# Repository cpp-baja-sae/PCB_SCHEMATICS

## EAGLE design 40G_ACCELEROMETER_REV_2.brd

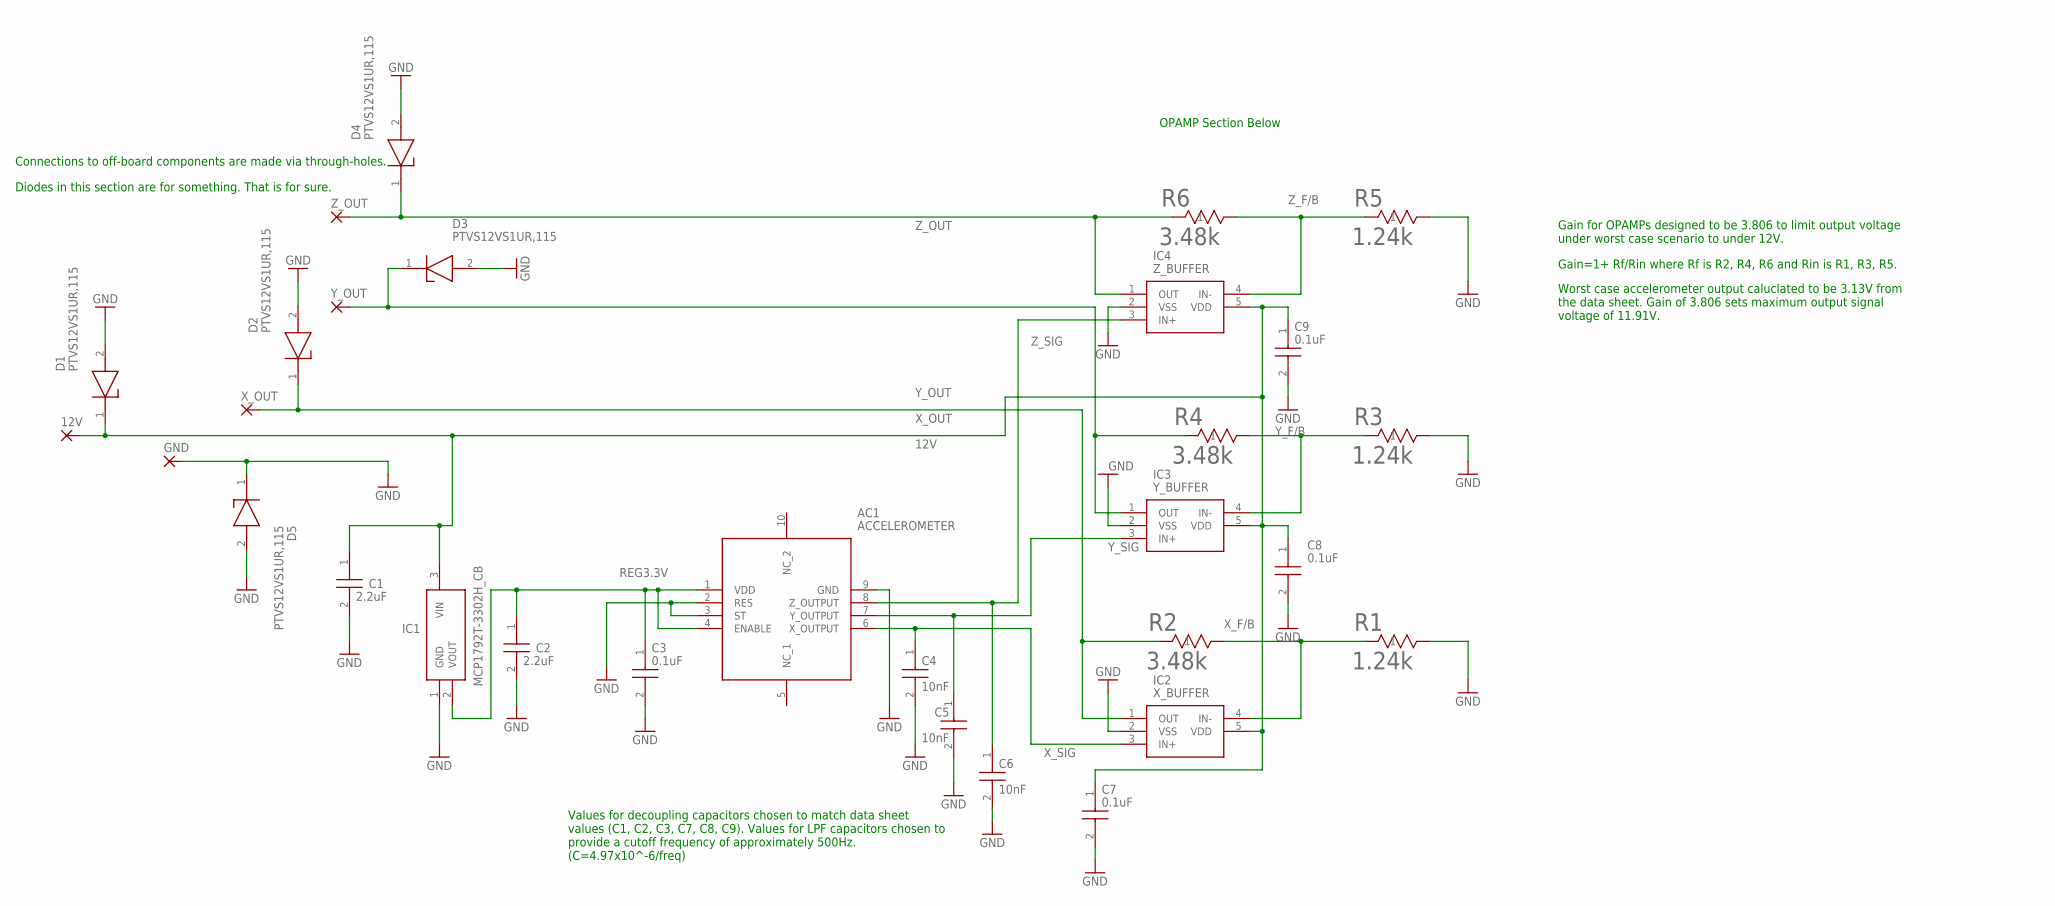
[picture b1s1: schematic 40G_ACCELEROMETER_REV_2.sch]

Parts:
12V: 2,54/1,1
AC1: ACCELEROMETER; KX2201072
C1, C2: 2.2uF; CAPC1608X90N
C3, C7, C8, C9: 0.1uF; CAPC1608X90N
C4, C5, C6: 10nF; CAPC1608X90N
D1, D2, D3, D4, D5: PTVS12VS1UR,115; SOD123W
GND: 2,54/1,1
IC1: MCP1792T-3302H_CB; SOT95P255X145-3N
IC2: X_BUFFER; SOT95P275X110-5N
IC3: Y_BUFFER; SOT95P275X110-5N
IC4: Z_BUFFER; SOT95P275X110-5N
R1, R3, R5: 1.24k; RES_TNPW0402_VIS
R2, R4, R6: 3.48k; RES_TNPW0402_VIS
X_OUT: 2,54/1,1
Y_OUT: 2,54/1,1
Z_OUT: 2,54/1,1

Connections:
12V: 12V.1, C1.1, C7.1, C8.1, C9.1, D1.1 (K), IC1.3 (VIN), IC2.5 (VDD), IC3.5 (VDD), IC4.5 (VDD)
GND: AC1.2 (RES), AC1.3 (ST), AC1.9 (GND), C1.2, C2.2, C3.2, C4.2, C5.2, C6.2, C7.2, C8.2, C9.2, D1.2 (A), D2.2 (A), D3.2 (A), D4.2 (A), D5.1 (K), D5.2 (A), GND.1, IC1.1 (GND), IC2.2 (VSS), IC3.2 (VSS), IC4.2 (VSS), R1.2, R3.2, R5.2
REG3.3V: AC1.1 (VDD), AC1.4 (ENABLE), C2.1, C3.1, IC1.2 (VOUT)
X_F/B: IC2.4 (IN-), R1.1, R2.2
X_OUT: D2.1 (K), IC2.1 (OUT), R2.1, X_OUT.1
X_SIG: AC1.6 (X_OUTPUT), C4.1, IC2.3 (IN+)
Y_F/B: IC3.4 (IN-), R3.1, R4.2
Y_OUT: D3.1 (K), IC3.1 (OUT), R4.1, Y_OUT.1
Y_SIG: AC1.7 (Y_OUTPUT), C5.1, IC3.3 (IN+)
Z_F/B: IC4.4 (IN-), R5.1, R6.2
Z_OUT: D4.1 (K), IC4.1 (OUT), R6.1, Z_OUT.1
Z_SIG: AC1.8 (Z_OUTPUT), C6.1, IC4.3 (IN+)

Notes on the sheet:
Gain for OPAMPs designed to be 3.806 to limit output voltage under worst case scenario to under 12V.
Values for decoupling capacitors chosen to match data sheet values (C1, C2, C3, C7, C8, C9). Values for LPF capacitors chosen to provide a cutoff frequency of approximately 500Hz. (C=4.97x10^-6/freq)
OPAMP Section Below
Gain=1+ Rf/Rin where Rf is R2, R4, R6 and Rin is R1, R3, R5.
Worst case accelerometer output caluclated to be 3.13V from the data sheet. Gain of 3.806 sets maximum output signal voltage of 11.91V.
Diodes in this section are for something. That is for sure.
Connections to off-board components are made via through-holes.

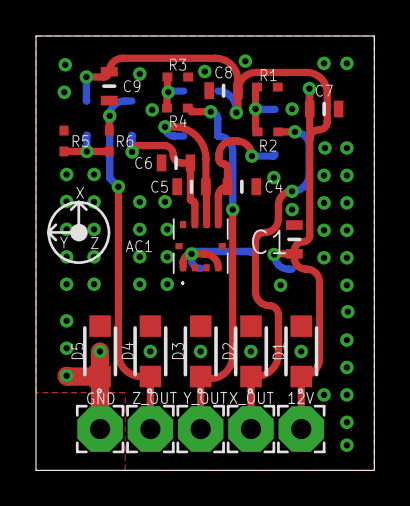
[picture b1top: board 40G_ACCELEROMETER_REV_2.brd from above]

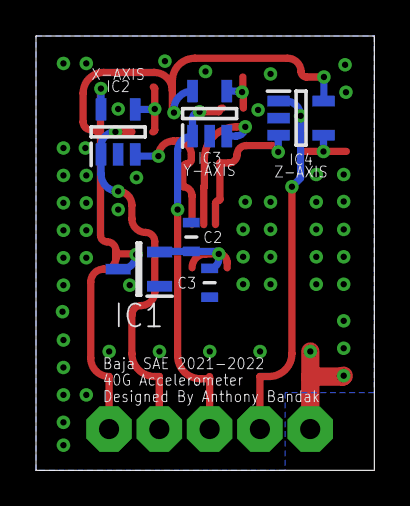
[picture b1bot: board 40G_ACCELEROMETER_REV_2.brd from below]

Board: 2 copper layers, 18.8 x 24.1 mm, 30 parts (6 on the bottom side), 12 nets.

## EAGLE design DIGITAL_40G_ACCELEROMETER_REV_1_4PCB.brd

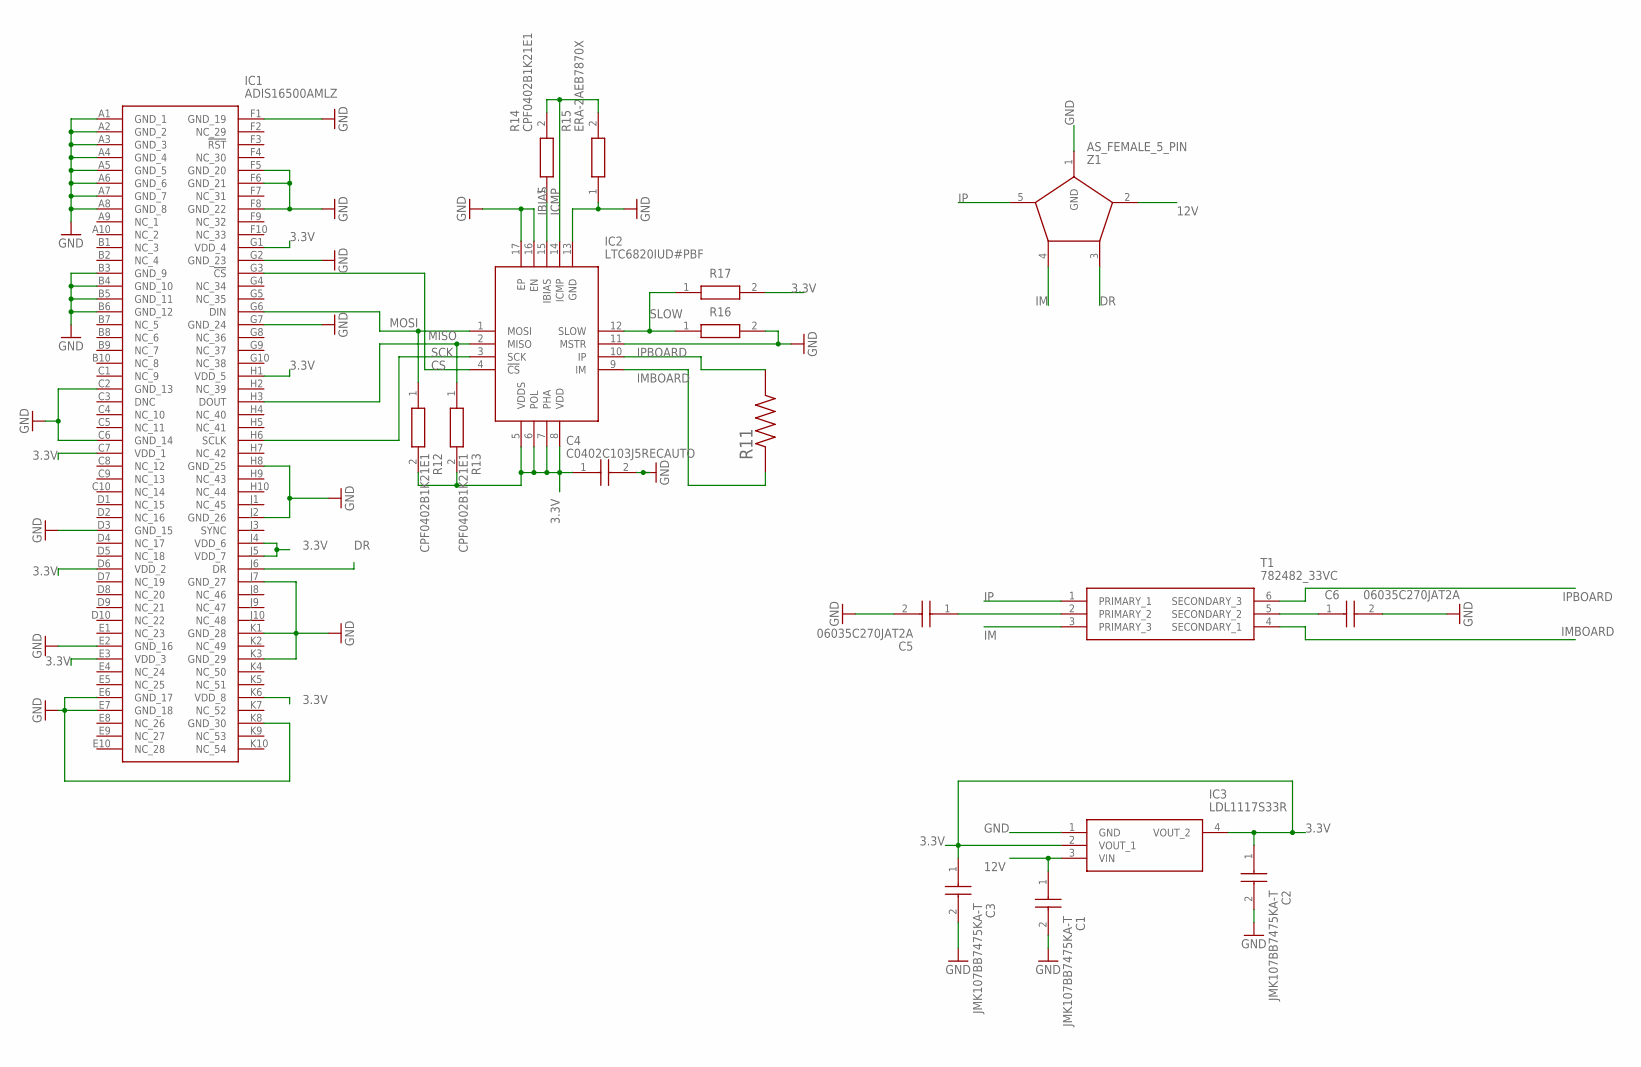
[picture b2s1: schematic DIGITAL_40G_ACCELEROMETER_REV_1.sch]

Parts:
C1, C2, C3: JMK107BB7475KA-T; CAPC1608X90N
C4: C0402C103J5RECAUTO; CAPC1005X55N
C5, C6: 06035C270JAT2A; CAPC1608X90N
IC1: ADIS16500AMLZ; BGA100C127P10X10_1500X1500X608
IC2: LTC6820IUD#PBF; QFN50P300X300X80-17N
IC3: LDL1117S33R; SOT230P700X180-4N
R11: 100; RESC1005X40N
R12, R13, R14: CPF0402B1K21E1; RESC1005X35N
R15: ERA-2AEB7870X; ERA2AED122X
R16, R17: CRG0402ZR; RESC1005X40N
T1: 782482_33VC; DIP1016W60P254L914H635Q6N
Z1: AS_FEMALE_5_PIN

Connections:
3.3V: C2.1, C3.1, C4.1, IC1.C7 (VDD_1), IC1.D6 (VDD_2), IC1.E3 (VDD_3), IC1.G1 (VDD_4), IC1.H1 (VDD_5), IC1.J4 (VDD_6), IC1.J5 (VDD_7), IC1.K6 (VDD_8), IC2.5 (VDDS), IC2.6 (POL), IC2.7 (PHA), IC2.8 (VDD), IC3.2 (VOUT_1), IC3.4 (VOUT_2), R12.2, R13.2, R17.2
12V: C1.1, IC3.3 (VIN), Z1.2 (1)
CS: IC1.G3 (!CS), IC2.4 (!CS)
DR: IC1.J6 (DR), Z1.3 (2)
GND: C1.2, C2.2, C3.2, C4.2, C5.2, C6.2, IC1.A1 (GND_1), IC1.A2 (GND_2), IC1.A3 (GND_3), IC1.A4 (GND_4), IC1.A5 (GND_5), IC1.A6 (GND_6), IC1.A7 (GND_7), IC1.A8 (GND_8), IC1.B3 (GND_9), IC1.B4 (GND_10), IC1.B5 (GND_11), IC1.B6 (GND_12), IC1.C2 (GND_13), IC1.C6 (GND_14), IC1.D3 (GND_15), IC1.E2 (GND_16), IC1.E6 (GND_17), IC1.E7 (GND_18), IC1.F1 (GND_19), IC1.F5 (GND_20), IC1.F6 (GND_21), IC1.F8 (GND_22), IC1.G2 (GND_23), IC1.G7 (GND_24), IC1.H8 (GND_25), IC1.J2 (GND_26), IC1.J7 (GND_27), IC1.K1 (GND_28), IC1.K3 (GND_29), IC1.K8 (GND_30), IC2.11 (MSTR), IC2.13 (GND), IC2.16 (EN), IC2.17 (EP), IC3.1 (GND), R15.1, R16.2, Z1.1 (GND)
IBIAS: IC2.15 (IBIAS), R14.1
ICMP: IC2.14 (ICMP), R14.2, R15.2
IM: T1.3 (PRIMARY_3), Z1.4 (3)
IMBOARD: IC2.9 (IM), R11.1, T1.4 (SECONDARY_1)
IP: T1.1 (PRIMARY_1), Z1.5 (4)
IPBOARD: IC2.10 (IP), R11.2, T1.6 (SECONDARY_3)
MISO: IC1.H3 (DOUT), IC2.2 (MISO), R13.1
MOSI: IC1.G6 (DIN), IC2.1 (MOSI), R12.1
unnamed: C6.1, T1.5 (SECONDARY_2)
unnamed: C5.1, T1.2 (PRIMARY_2)
SCK: IC1.H6 (SCLK), IC2.3 (SCK)
SLOW: IC2.12 (SLOW), R16.1, R17.1

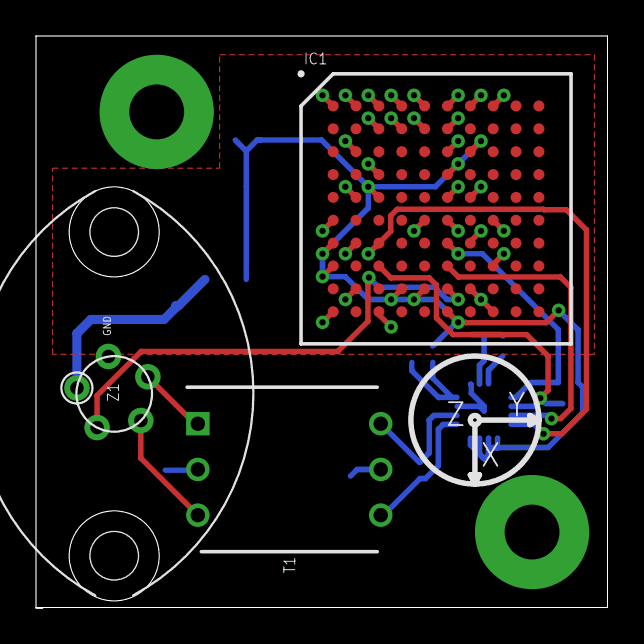
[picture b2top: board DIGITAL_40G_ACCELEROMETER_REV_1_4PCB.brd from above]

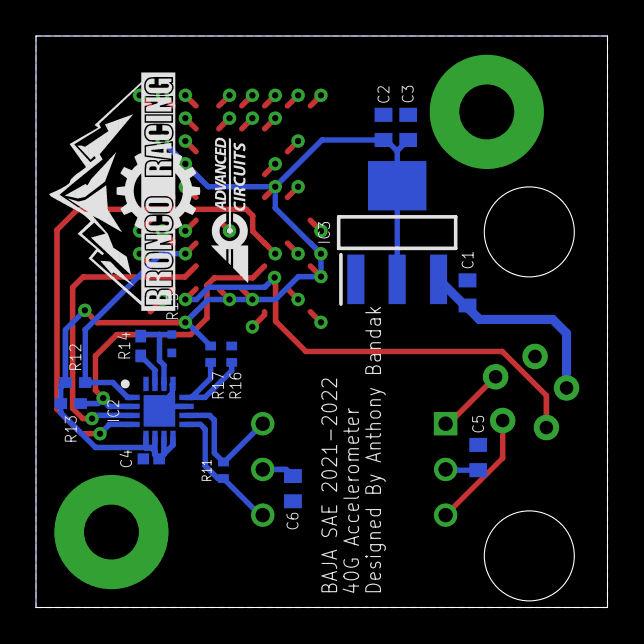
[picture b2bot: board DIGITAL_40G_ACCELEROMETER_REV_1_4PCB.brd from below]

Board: 2 copper layers, 31.8 x 31.8 mm, 20 parts (16 on the bottom side), 17 nets.

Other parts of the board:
U$3, U$4: THROUGH_HOLE; 1/16TH_BOLT

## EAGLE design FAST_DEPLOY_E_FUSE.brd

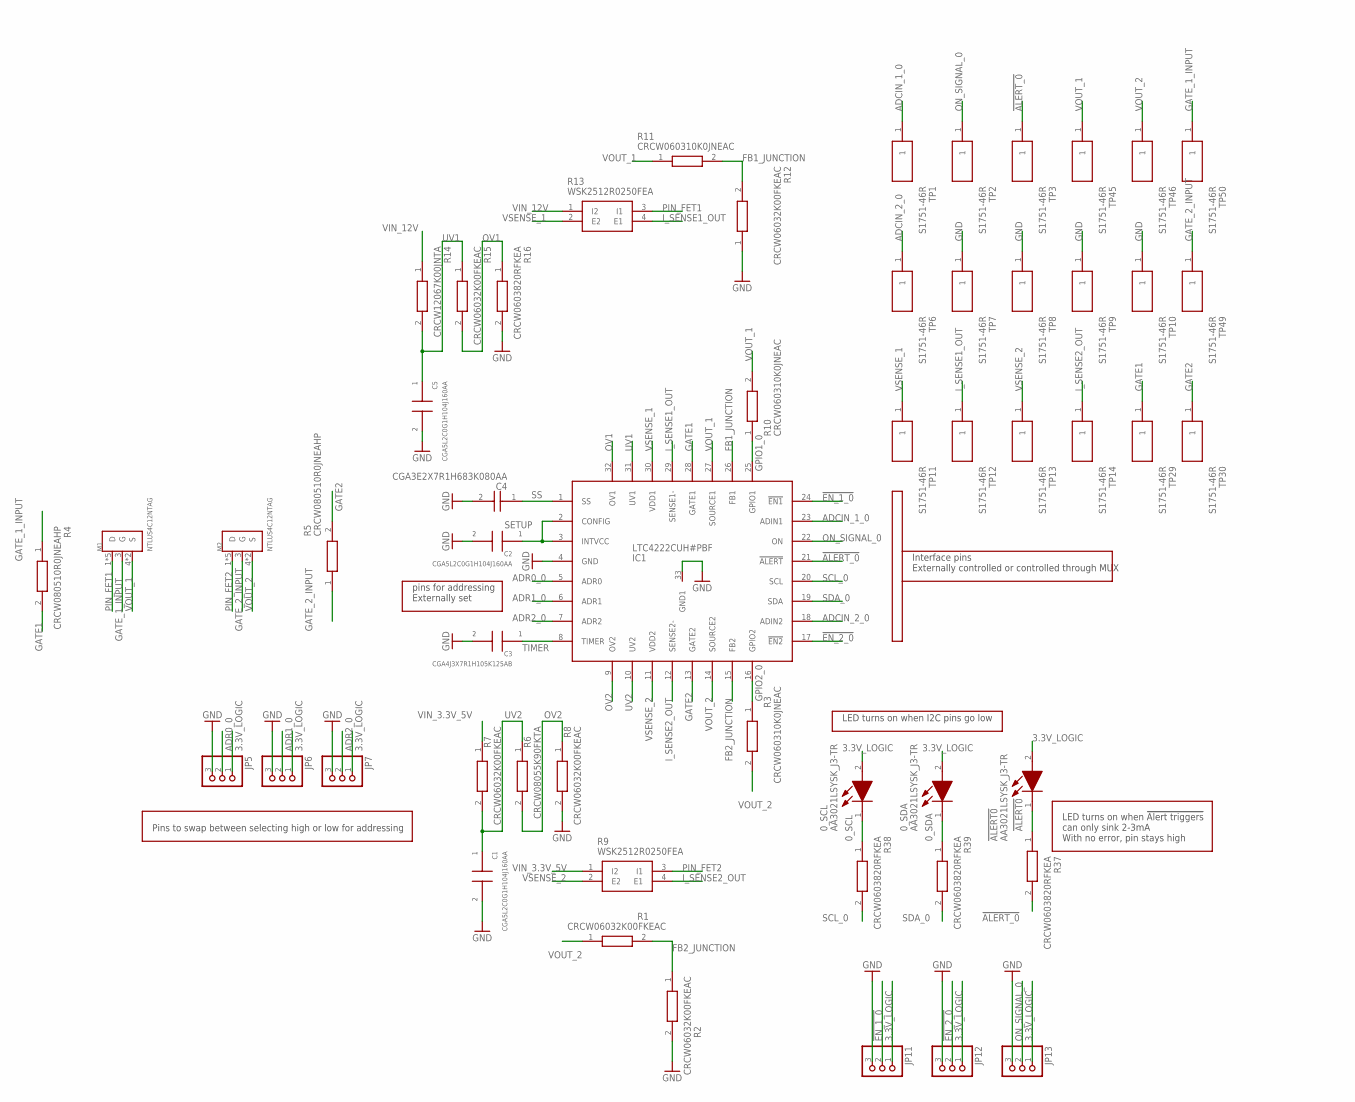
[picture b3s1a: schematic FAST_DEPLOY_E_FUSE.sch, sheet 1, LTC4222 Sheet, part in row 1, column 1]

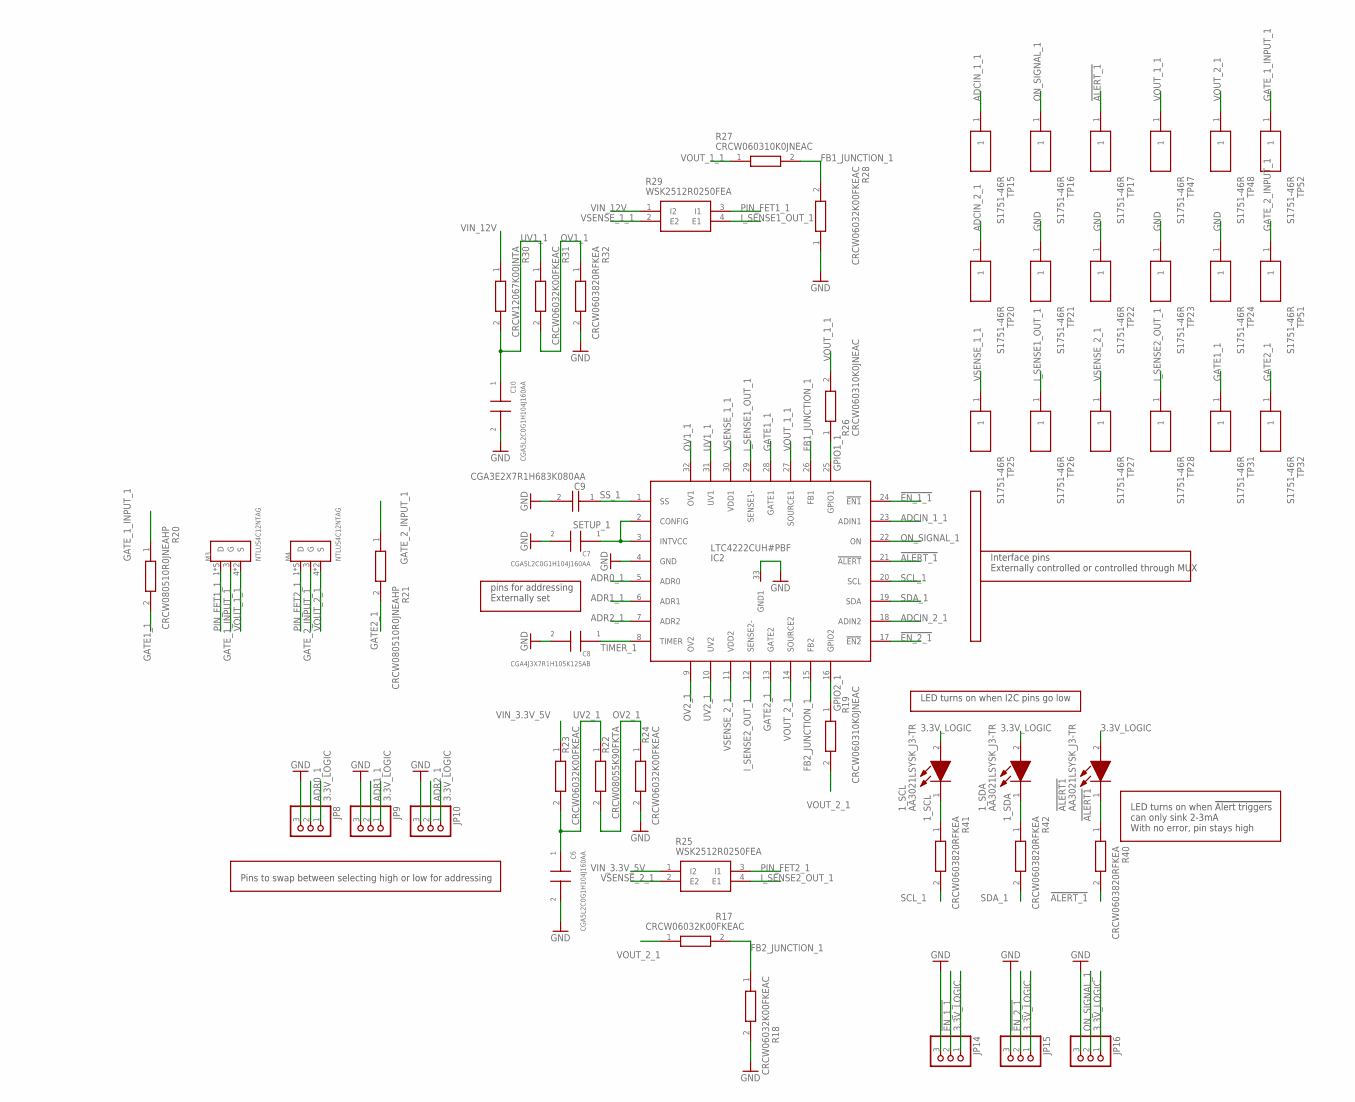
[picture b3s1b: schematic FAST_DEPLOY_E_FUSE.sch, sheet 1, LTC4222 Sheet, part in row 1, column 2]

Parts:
0_SCL, 0_SDA, 1_SCL, 1_SDA: AA3021LSYSK_J3-TR; AA3021LSYSKJ3TR
!ALERT0, !ALERT1: AA3021LSYSK_J3-TR; AA3021LSYSKJ3TR
C1, C2, C5, C6, C7, C10: CGA5L2C0G1H104J160AA; CAPC3216X180N
C3, C8: CGA4J3X7R1H105K125AB; CAPC2012X145N
C4, C9: CGA3E2X7R1H683K080AA; CAPC1608X90N
IC1, IC2: LTC4222CUH#PBF; QFN50P500X500X80-33T345N
JP5, JP6, JP7, JP8, JP9, JP10, JP11, JP12, JP13, JP14, JP15, JP16: PINHD-1X3; 1X03
M1, M2, M3, M4: NTLUS4C12NTAG; TRANS_NTLUS3A18PZTAG
R1, R2, R7, R8, R12, R15, R17, R18, R23, R24, R28, R31: CRCW06032K00FKEAC; RESC1608X55N
R3, R10, R11, R19, R26, R27: CRCW060310K0JNEAC; RESC1608X55N
R4, R5, R20, R21: CRCW080510R0JNEAHP; RESC2012X60N
R6, R22: CRCW08055K90FKTA; RESC2012X50N
R9, R13, R25, R29: WSK2512R0250FEA; WSK2512R0100FEA
R14, R30: CRCW12067K00JNTA; RESC3216X60N
R16, R32, R37, R38, R39, R40, R41, R42: CRCW0603820RFKEA; RESC1608X50N
TP1, TP2, TP3, TP6, TP7, TP8, TP9, TP10, TP11, TP12, TP13, TP14, TP15, TP16, TP17, TP20, TP21, TP22, TP23, TP24, TP25, TP26, TP27, TP28, TP29, TP30, TP31, TP32, TP45, TP46, TP47, TP48, TP49, TP50, TP51, TP52: S1751-46R; S175146R

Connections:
0_SCL: 0_SCL.1 (K), R38.1
0_SDA: 0_SDA.1 (K), R39.1
1_SCL: 1_SCL.1 (K), R41.1
1_SDA: 1_SDA.1 (K), R42.1
3.3V_LOGIC: 0_SCL.2 (A), 0_SDA.2 (A), 1_SCL.2 (A), 1_SDA.2 (A), !ALERT0.2 (A), !ALERT1.2 (A), JP5.1, JP6.1, JP7.1, JP8.1, JP9.1, JP10.1, JP11.1, JP12.1, JP13.1, JP14.1, JP15.1, JP16.1; also elsewhere on the board
!ALERT0: !ALERT0.1 (K), R37.1
!ALERT1: !ALERT1.1 (K), R40.1
!ALERT_0: IC1.21 (!ALERT), R37.2, TP3.1; also elsewhere on the board
!ALERT_1: IC2.21 (!ALERT), R40.2, TP17.1; also elsewhere on the board
!EN_1_0: IC1.24 (!EN1), JP11.2
!EN_1_1: IC2.24 (!EN1), JP14.2
!EN_2_0: IC1.17 (!EN2), JP12.2
!EN_2_1: IC2.17 (!EN2), JP15.2
ADCIN_1_0: IC1.23 (ADIN1), TP1.1; also elsewhere on the board
ADCIN_1_1: IC2.23 (ADIN1), TP15.1; also elsewhere on the board
ADCIN_2_0: IC1.18 (ADIN2), TP6.1; also elsewhere on the board
ADCIN_2_1: IC2.18 (ADIN2), TP20.1; also elsewhere on the board
ADR0_0: IC1.5 (ADR0), JP5.2
ADR0_1: IC2.5 (ADR0), JP8.2
ADR1_0: IC1.6 (ADR1), JP6.2
ADR1_1: IC2.6 (ADR1), JP9.2
ADR2_0: IC1.7 (ADR2), JP7.2
ADR2_1: IC2.7 (ADR2), JP10.2
FB1_JUNCTION: IC1.26 (FB1), R11.2, R12.2
FB1_JUNCTION_1: IC2.26 (FB1), R27.2, R28.2
FB2_JUNCTION: IC1.15 (FB2), R1.2, R2.1
FB2_JUNCTION_1: IC2.15 (FB2), R17.2, R18.1
GATE1: IC1.28 (GATE1), R4.2, TP29.1
GATE1_1: IC2.28 (GATE1), R20.2, TP31.1
GATE2: IC1.13 (GATE2), R5.2, TP30.1
GATE2_1: IC2.13 (GATE2), R21.2, TP32.1
GATE_1_INPUT: M1.3 (G), R4.1, TP50.1
GATE_1_INPUT_1: M3.3 (G), R20.1, TP52.1
GATE_2_INPUT: M2.3 (G), R5.1, TP49.1
GATE_2_INPUT_1: M4.3 (G), R21.1, TP51.1
GND: C1.2, C2.2, C3.2, C4.2, C5.2, C6.2, C7.2, C8.2, C9.2, C10.2, IC1.4 (GND), IC1.33 (GND1), IC2.4 (GND), IC2.33 (GND1), JP5.3, JP6.3, JP7.3, JP8.3, JP9.3, JP10.3, JP11.3, JP12.3, JP13.3, JP14.3, JP15.3, JP16.3, R2.2, R8.2, R12.1, R16.2, R18.2, R24.2, R28.1, R32.2, TP7.1, TP8.1, TP9.1, TP10.1, TP21.1, TP22.1, TP23.1, TP24.1; also elsewhere on the board
GPIO1_0: IC1.25 (GPIO1), R10.1
GPIO1_1: IC2.25 (GPIO1), R26.1
GPIO2_0: IC1.16 (GPIO2), R3.1
GPIO2_1: IC2.16 (GPIO2), R19.1
I_SENSE1_OUT: IC1.29 (SENSE1-), R13.4 (E1), TP12.1
I_SENSE1_OUT_1: IC2.29 (SENSE1-), R29.4 (E1), TP26.1
I_SENSE2_OUT: IC1.12 (SENSE2-), R9.4 (E1), TP14.1
I_SENSE2_OUT_1: IC2.12 (SENSE2-), R25.4 (E1), TP28.1
ON_SIGNAL_0: IC1.22 (ON), JP13.2, TP2.1
ON_SIGNAL_1: IC2.22 (ON), JP16.2, TP16.1
OV1: IC1.32 (OV1), R15.2, R16.1
OV1_1: IC2.32 (OV1), R31.2, R32.1
OV2: IC1.9 (OV2), R6.2, R8.1
OV2_1: IC2.9 (OV2), R22.2, R24.1
PIN_FET1: M1.1 (D), M1.2 (D), M1.5 (D), M1.6 (D), M1.7 (D), R13.3 (I1)
PIN_FET1_1: M3.1 (D), M3.2 (D), M3.5 (D), M3.6 (D), M3.7 (D), R29.3 (I1)
PIN_FET2: M2.1 (D), M2.2 (D), M2.5 (D), M2.6 (D), M2.7 (D), R9.3 (I1)
PIN_FET2_1: M4.1 (D), M4.2 (D), M4.5 (D), M4.6 (D), M4.7 (D), R25.3 (I1)
SCL_0: IC1.20 (SCL), R38.2; also elsewhere on the board
SCL_1: IC2.20 (SCL), R41.2; also elsewhere on the board
SDA_0: IC1.19 (SDA), R39.2; also elsewhere on the board
SDA_1: IC2.19 (SDA), R42.2; also elsewhere on the board
SETUP: C2.1, IC1.2 (CONFIG), IC1.3 (INTVCC)
SETUP_1: C7.1, IC2.2 (CONFIG), IC2.3 (INTVCC)
SS: C4.1, IC1.1 (SS)
SS_1: C9.1, IC2.1 (SS)
TIMER: C3.1, IC1.8 (TIMER)
TIMER_1: C8.1, IC2.8 (TIMER)
UV1: C5.1, IC1.31 (UV1), R14.2, R15.1
UV1_1: C10.1, IC2.31 (UV1), R30.2, R31.1
UV2: C1.1, IC1.10 (UV2), R6.1, R7.2
UV2_1: C6.1, IC2.10 (UV2), R22.1, R23.2
VIN_3.3V_5V: R7.1, R9.1 (I2), R23.1, R25.1 (I2); also elsewhere on the board
VIN_12V: R13.1 (I2), R14.1, R29.1 (I2), R30.1; also elsewhere on the board
VOUT_1: IC1.27 (SOURCE1), M1.4 (S), M1.8 (S), R10.2, R11.1, TP45.1; also elsewhere on the board
VOUT_1_1: IC2.27 (SOURCE1), M3.4 (S), M3.8 (S), R26.2, R27.1, TP47.1; also elsewhere on the board
VOUT_2: IC1.14 (SOURCE2), M2.4 (S), M2.8 (S), R1.1, R3.2, TP46.1; also elsewhere on the board
VOUT_2_1: IC2.14 (SOURCE2), M4.4 (S), M4.8 (S), R17.1, R19.2, TP48.1; also elsewhere on the board
VSENSE_1: IC1.30 (VDD1), R13.2 (E2), TP11.1
VSENSE_1_1: IC2.30 (VDD1), R29.2 (E2), TP25.1
VSENSE_2: IC1.11 (VDD2), R9.2 (E2), TP13.1
VSENSE_2_1: IC2.11 (VDD2), R25.2 (E2), TP27.1

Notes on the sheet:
pins for addressing Externally set
Interface pins Externally controlled or controlled through MUX
Pins to swap between selecting high or low for addressing
LED turns on when !Alert triggers can only sink 2-3mA With no error, pin stays high
LED turns on when I2C pins go low

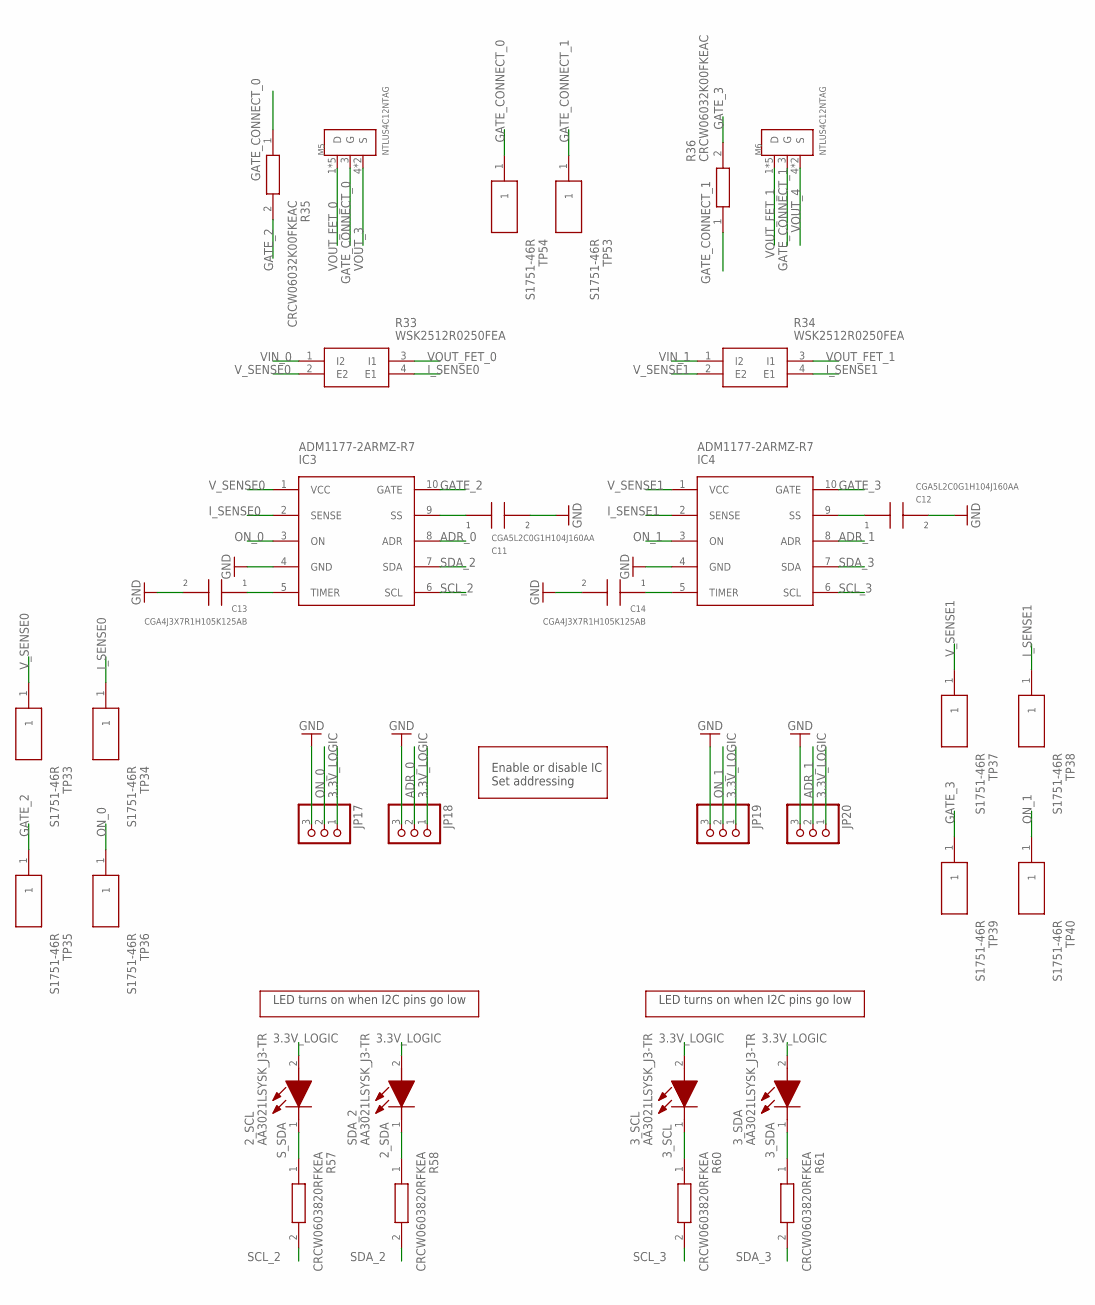
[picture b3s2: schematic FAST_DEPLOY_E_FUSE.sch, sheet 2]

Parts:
2_SCL, 3_SCL, 3_SDA: AA3021LSYSK_J3-TR; AA3021LSYSKJ3TR
C11, C12: CGA5L2C0G1H104J160AA; CAPC3216X180N
C13, C14: CGA4J3X7R1H105K125AB; CAPC2012X145N
IC3, IC4: ADM1177-2ARMZ-R7; SOP50P490X110-10N
JP17, JP18, JP19, JP20: PINHD-1X3; 1X03
M5, M6: NTLUS4C12NTAG; TRANS_NTLUS3A18PZTAG
R33, R34: WSK2512R0250FEA; WSK2512R0100FEA
R35, R36: CRCW06032K00FKEAC; RESC1608X55N
R57, R58, R60, R61: CRCW0603820RFKEA; RESC1608X50N
SDA_2: AA3021LSYSK_J3-TR; AA3021LSYSKJ3TR
TP33, TP34, TP35, TP36, TP37, TP38, TP39, TP40, TP53, TP54: S1751-46R; S175146R

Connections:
2_SDA: R58.1, SDA_2.1 (K)
3.3V_LOGIC: 2_SCL.2 (A), 3_SCL.2 (A), 3_SDA.2 (A), JP17.1, JP18.1, JP19.1, JP20.1, SDA_2.2 (A); also elsewhere on the board
3_SCL: 3_SCL.1 (K), R60.1
3_SDA: 3_SDA.1 (K), R61.1
ADR_0: IC3.8 (ADR), JP18.2
ADR_1: IC4.8 (ADR), JP20.2
GATE_2: IC3.10 (GATE), R35.2, TP35.1
GATE_3: IC4.10 (GATE), R36.2, TP39.1
GATE_CONNECT_0: M5.3 (G), R35.1, TP54.1
GATE_CONNECT_1: M6.3 (G), R36.1, TP53.1
GND: C11.2, C12.2, C13.2, C14.2, IC3.4 (GND), IC4.4 (GND), JP17.3, JP18.3, JP19.3, JP20.3; also elsewhere on the board
I_SENSE0: IC3.2 (SENSE), R33.4 (E1), TP34.1
I_SENSE1: IC4.2 (SENSE), R34.4 (E1), TP38.1
unnamed: C11.1, IC3.9 (SS)
unnamed: C13.1, IC3.5 (TIMER)
unnamed: C14.1, IC4.5 (TIMER)
unnamed: C12.1, IC4.9 (SS)
ON_0: IC3.3 (ON), JP17.2, TP36.1
ON_1: IC4.3 (ON), JP19.2, TP40.1
SCL_2: IC3.6 (SCL), R57.2; also elsewhere on the board
SCL_3: IC4.6 (SCL), R60.2; also elsewhere on the board
SDA_2: IC3.7 (SDA), R58.2; also elsewhere on the board
SDA_3: IC4.7 (SDA), R61.2; also elsewhere on the board
S_SDA: 2_SCL.1 (K), R57.1
VIN_0: R33.1 (I2); also elsewhere on the board
VIN_1: R34.1 (I2); also elsewhere on the board
VOUT_3: M5.4 (S), M5.8 (S); also elsewhere on the board
VOUT_4: M6.4 (S), M6.8 (S); also elsewhere on the board
VOUT_FET_0: M5.1 (D), M5.2 (D), M5.5 (D), M5.6 (D), M5.7 (D), R33.3 (I1)
VOUT_FET_1: M6.1 (D), M6.2 (D), M6.5 (D), M6.6 (D), M6.7 (D), R34.3 (I1)
V_SENSE0: IC3.1 (VCC), R33.2 (E2), TP33.1
V_SENSE1: IC4.1 (VCC), R34.2 (E2), TP37.1

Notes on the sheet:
Enable or disable IC Set addressing
LED turns on when I2C pins go low

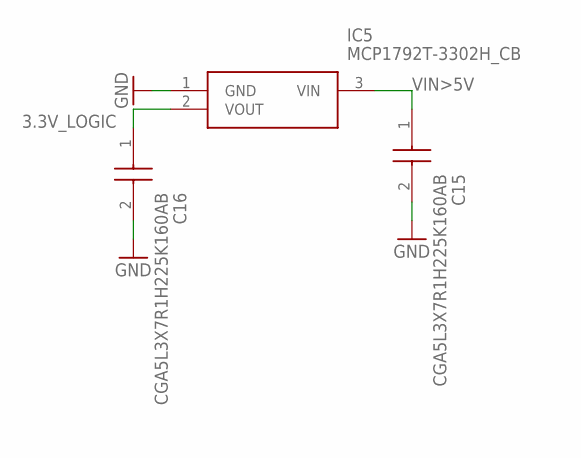
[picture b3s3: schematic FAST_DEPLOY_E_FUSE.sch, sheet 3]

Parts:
C15, C16: CGA5L3X7R1H225K160AB; CAPC3216X190N
IC5: MCP1792T-3302H_CB; SOT95P255X145-3N

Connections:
3.3V_LOGIC: C16.1, IC5.2 (VOUT); also elsewhere on the board
GND: C15.2, C16.2, IC5.1 (GND); also elsewhere on the board
VIN>5V: C15.1, IC5.3 (VIN); also elsewhere on the board

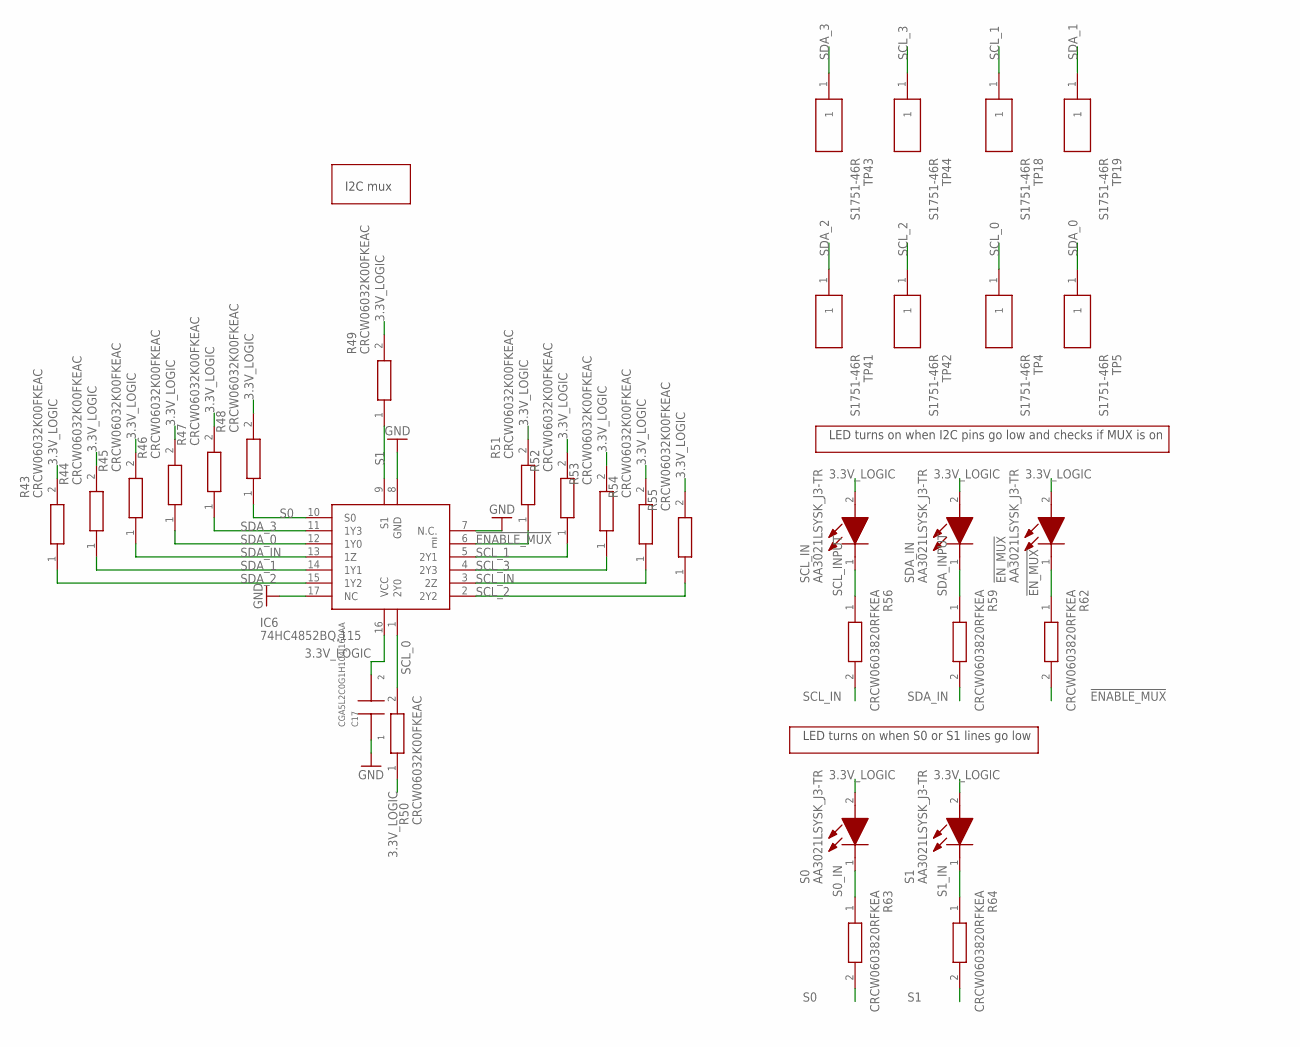
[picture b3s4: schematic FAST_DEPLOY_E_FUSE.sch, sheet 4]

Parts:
!EN_MUX: AA3021LSYSK_J3-TR; AA3021LSYSKJ3TR
C17: CGA5L2C0G1H104J160AA; CAPC3216X180N
IC6: 74HC4852BQ,115; 74HCT595BQ115
R43, R44, R45, R46, R47, R48, R49, R50, R51, R52, R53, R54, R55: CRCW06032K00FKEAC; RESC1608X55N
R56, R59, R62, R63, R64: CRCW0603820RFKEA; RESC1608X50N
S0, S1: AA3021LSYSK_J3-TR; AA3021LSYSKJ3TR
SCL_IN: AA3021LSYSK_J3-TR; AA3021LSYSKJ3TR
SDA_IN: AA3021LSYSK_J3-TR; AA3021LSYSKJ3TR
TP4, TP5, TP18, TP19, TP41, TP42, TP43, TP44: S1751-46R; S175146R

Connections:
3.3V_LOGIC: !EN_MUX.2 (A), C17.2, IC6.16 (VCC), R43.2, R44.2, R45.2, R46.2, R47.2, R48.2, R49.2, R50.1, R51.2, R52.2, R53.2, R54.2, R55.2, S0.2 (A), S1.2 (A), SCL_IN.2 (A), SDA_IN.2 (A); also elsewhere on the board
!ENABLE_MUX: IC6.6 (!E), R51.1, R62.2; also elsewhere on the board
!EN_MUX: !EN_MUX.1 (K), R62.1
GND: C17.1, IC6.7 (N.C.), IC6.8 (GND), IC6.17 (NC); also elsewhere on the board
S0: IC6.10 (S0), R48.1, R63.2; also elsewhere on the board
S0_IN: R63.1, S0.1 (K)
S1: IC6.9 (S1), R49.1, R64.2; also elsewhere on the board
S1_IN: R64.1, S1.1 (K)
SCL_0: IC6.1 (2Y0), R50.2, TP4.1; also elsewhere on the board
SCL_1: IC6.5 (2Y1), R52.1, TP18.1; also elsewhere on the board
SCL_2: IC6.2 (2Y2), R55.1, TP42.1; also elsewhere on the board
SCL_3: IC6.4 (2Y3), R53.1, TP44.1; also elsewhere on the board
SCL_IN: IC6.3 (2Z), R54.1, R56.2; also elsewhere on the board
SCL_INPUT: R56.1, SCL_IN.1 (K)
SDA_0: IC6.12 (1Y0), R46.1, TP5.1; also elsewhere on the board
SDA_1: IC6.14 (1Y1), R44.1, TP19.1; also elsewhere on the board
SDA_2: IC6.15 (1Y2), R43.1, TP41.1; also elsewhere on the board
SDA_3: IC6.11 (1Y3), R47.1, TP43.1; also elsewhere on the board
SDA_IN: IC6.13 (1Z), R45.1, R59.2; also elsewhere on the board
SDA_INPUT: R59.1, SDA_IN.1 (K)

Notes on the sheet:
LED turns on when I2C pins go low and checks if MUX is on
I2C mux
LED turns on when S0 or S1 lines go low

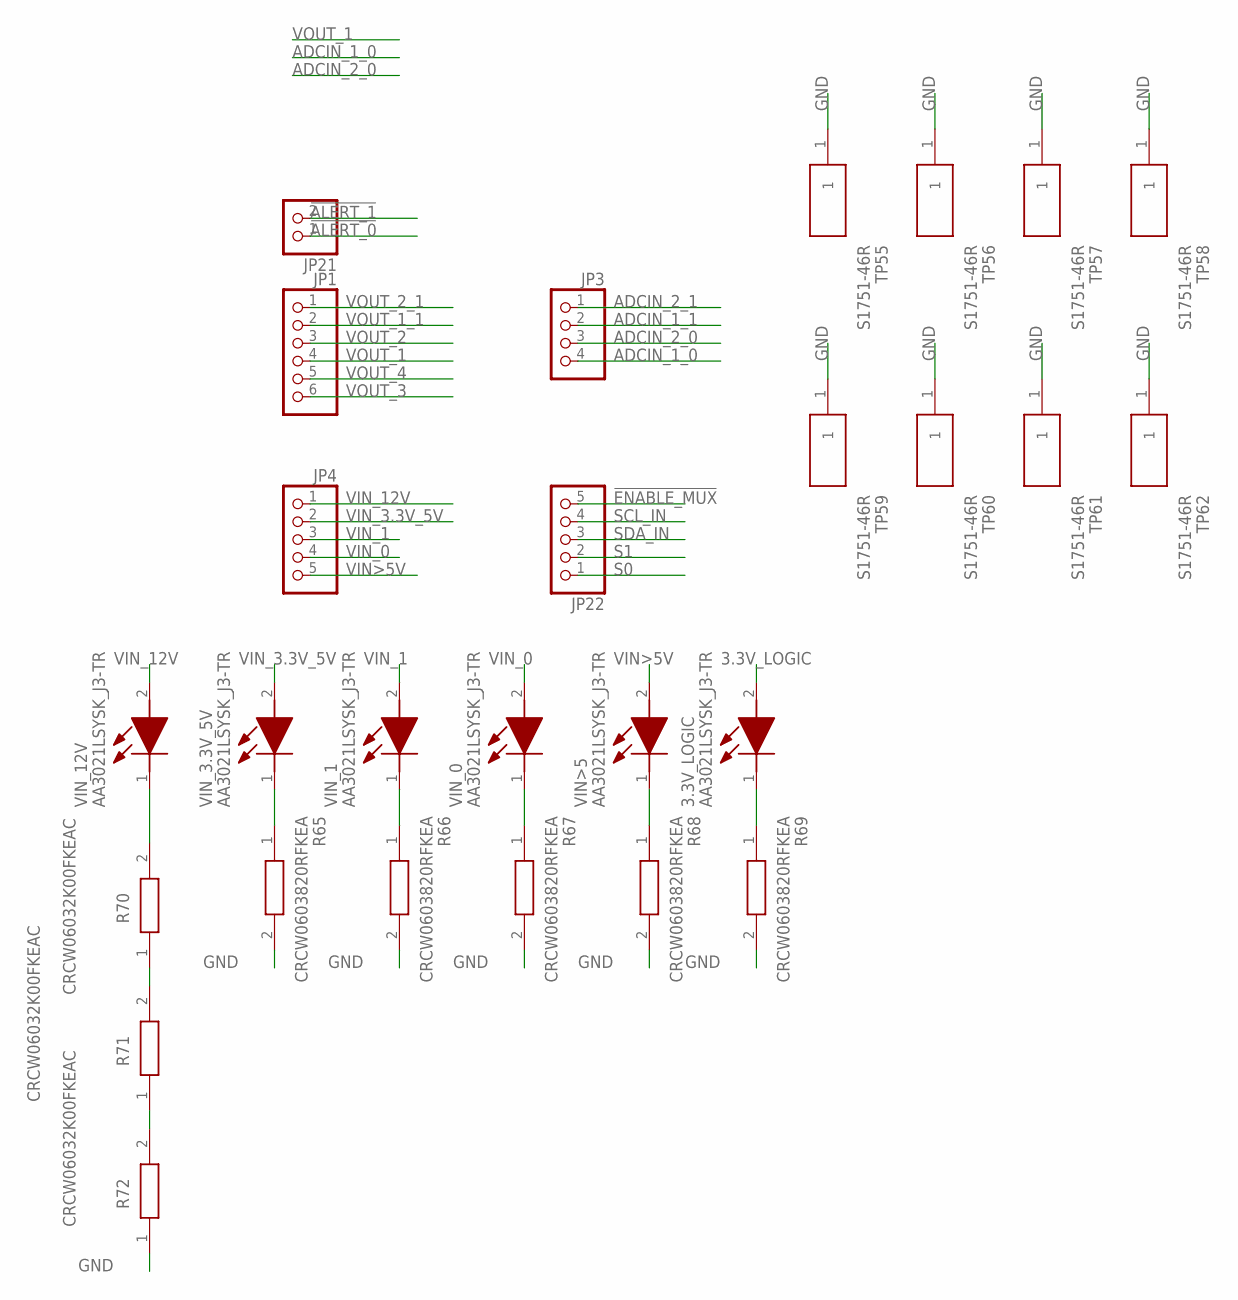
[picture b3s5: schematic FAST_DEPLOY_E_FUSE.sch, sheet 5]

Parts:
3.3V_LOGIC: AA3021LSYSK_J3-TR; AA3021LSYSKJ3TR
JP1: PINHD-1X6; 1X06
JP3: PINHD-1X4; 1X04
JP4, JP22: PINHD-1X5; 1X05
JP21: PINHD-1X2; 1X02
R65, R66, R67, R68, R69: CRCW0603820RFKEA; RESC1608X50N
R70, R71, R72: CRCW06032K00FKEAC; RESC1608X55N
TP55, TP56, TP57, TP58, TP59, TP60, TP61, TP62: S1751-46R; S175146R
VIN>5: AA3021LSYSK_J3-TR; AA3021LSYSKJ3TR
VIN_0, VIN_1, VIN_3.3V_5V, VIN_12V: AA3021LSYSK_J3-TR; AA3021LSYSKJ3TR

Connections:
3.3V_LOGIC: 3.3V_LOGIC.2 (A); also elsewhere on the board
!ALERT_0: JP21.1; also elsewhere on the board
!ALERT_1: JP21.2; also elsewhere on the board
!ENABLE_MUX: JP22.5; also elsewhere on the board
ADCIN_1_0: JP3.4; also elsewhere on the board
ADCIN_1_1: JP3.2; also elsewhere on the board
ADCIN_2_0: JP3.3; also elsewhere on the board
ADCIN_2_1: JP3.1; also elsewhere on the board
GND: R65.2, R66.2, R67.2, R68.2, R69.2, R72.1, TP55.1, TP56.1, TP57.1, TP58.1, TP59.1, TP60.1, TP61.1, TP62.1; also elsewhere on the board
unnamed: R70.1, R71.2
unnamed: R71.1, R72.2
unnamed: R70.2, VIN_12V.1 (K)
unnamed: R65.1, VIN_3.3V_5V.1 (K)
unnamed: R66.1, VIN_1.1 (K)
unnamed: R67.1, VIN_0.1 (K)
unnamed: R68.1, VIN>5.1 (K)
unnamed: 3.3V_LOGIC.1 (K), R69.1
S0: JP22.1; also elsewhere on the board
S1: JP22.2; also elsewhere on the board
SCL_IN: JP22.4; also elsewhere on the board
SDA_IN: JP22.3; also elsewhere on the board
VIN>5V: JP4.5, VIN>5.2 (A); also elsewhere on the board
VIN_0: JP4.4, VIN_0.2 (A); also elsewhere on the board
VIN_1: JP4.3, VIN_1.2 (A); also elsewhere on the board
VIN_3.3V_5V: JP4.2, VIN_3.3V_5V.2 (A); also elsewhere on the board
VIN_12V: JP4.1, VIN_12V.2 (A); also elsewhere on the board
VOUT_1: JP1.4; also elsewhere on the board
VOUT_1_1: JP1.2; also elsewhere on the board
VOUT_2: JP1.3; also elsewhere on the board
VOUT_2_1: JP1.1; also elsewhere on the board
VOUT_3: JP1.6; also elsewhere on the board
VOUT_4: JP1.5; also elsewhere on the board

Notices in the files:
parts and their libraries:
COPYRIGHT: Copyright (C) 2022 Ultra Librarian. All rights reserved.
